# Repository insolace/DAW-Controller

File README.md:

# DAW Controller
 Concept design for a DAW controller with LCD, encoders, and RGB pushbuttons.<br>
 Developed by Eric Bateman

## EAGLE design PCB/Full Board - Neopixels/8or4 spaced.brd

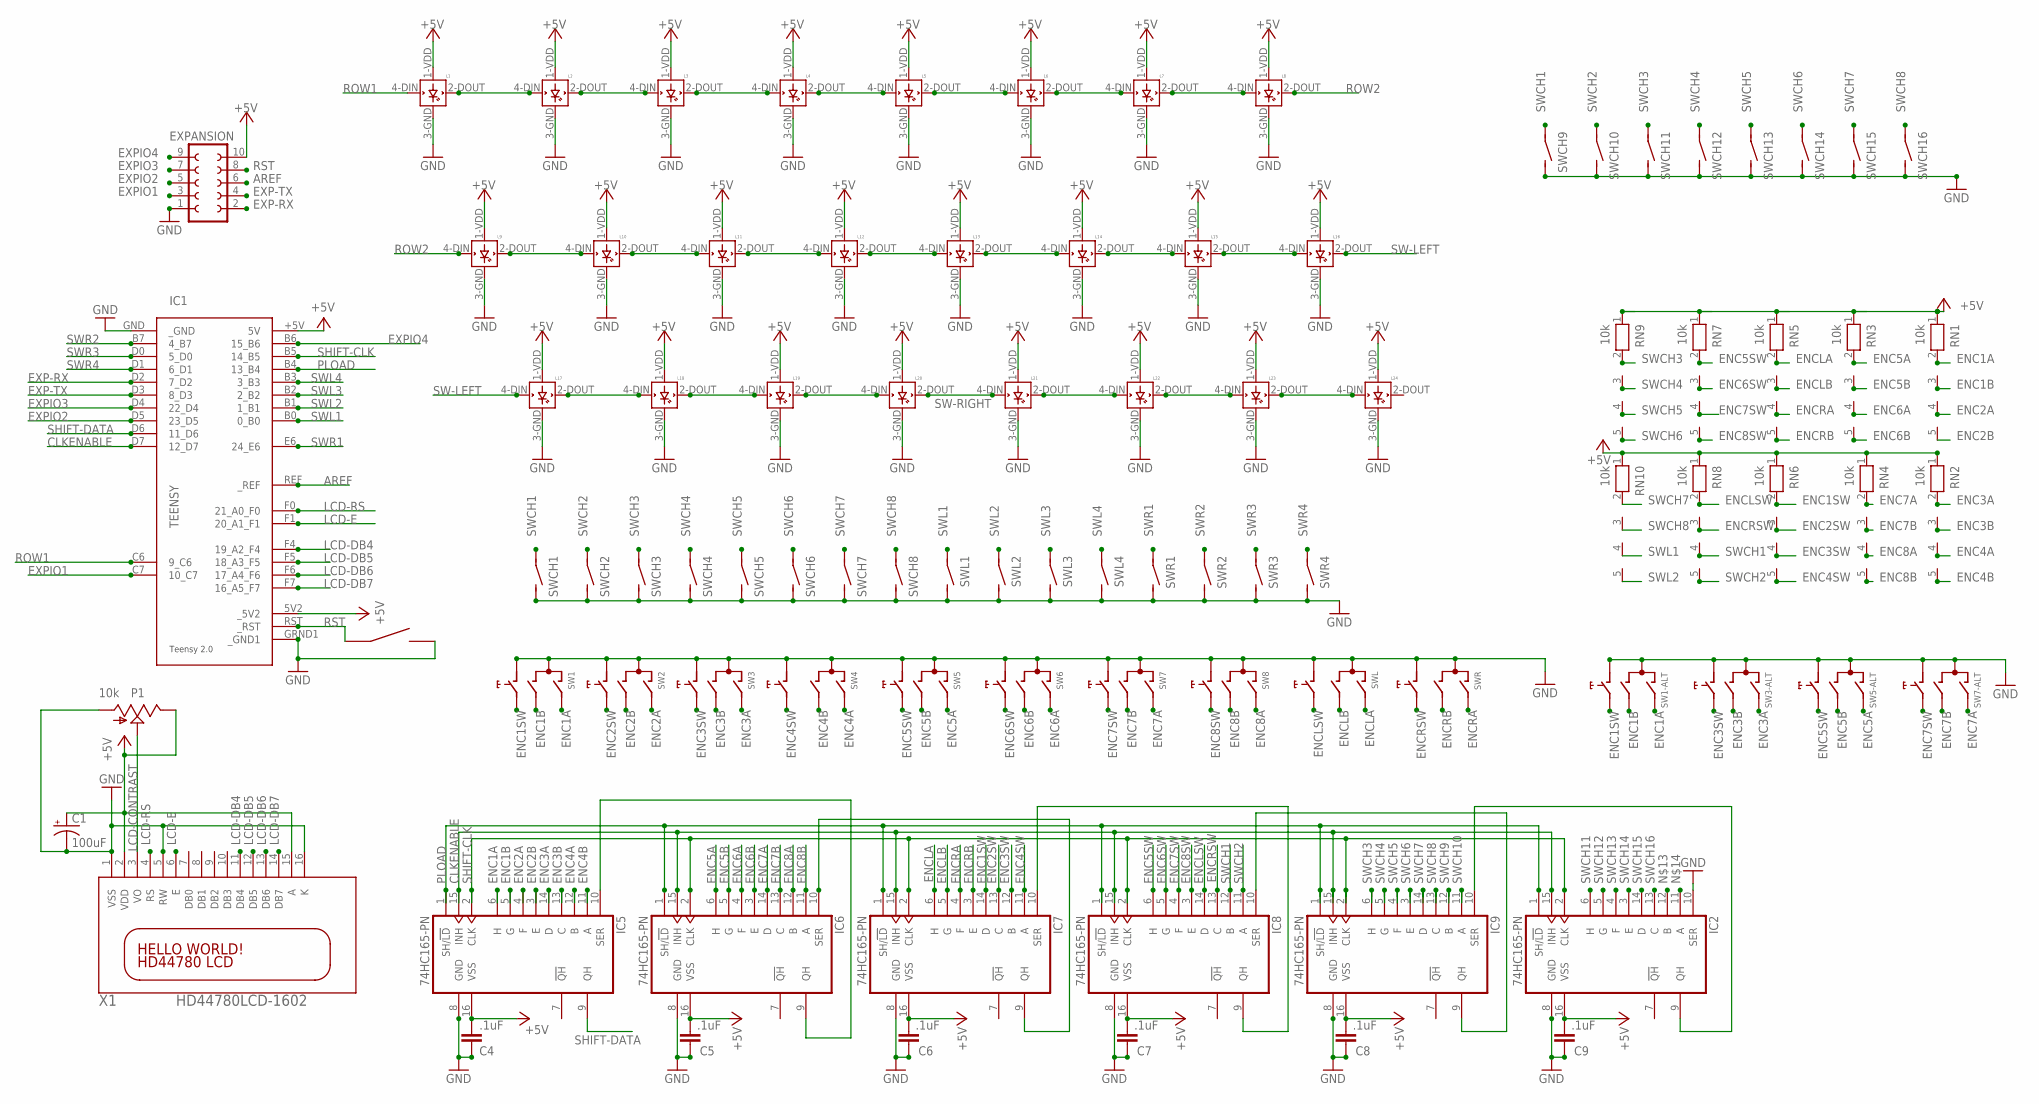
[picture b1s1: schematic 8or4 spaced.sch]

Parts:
C1: 100uF; E2,5-7
C4, C5, C6, C7, C8, C9: .1uF; C5B3.5
EXPANSION: FE05-2
IC1: TEENSY
IC2, IC5, IC6, IC7, IC8, IC9: 74HC165-PN; DIL16
L1, L2, L3, L4, L5, L6, L7, L8, L9, L10, L11, L12, L13, L14, L15, L16, L17, L18, L19, L20, L21, L22, L23, L24: WS2812B
P1: 10k; B25U
RN1, RN2, RN3, RN4, RN5, RN6, RN7, RN8, RN9, RN10: 10k; RN-5
SW1, SW1-ALT, SW2, SW3, SW3-ALT, SW4, SW5, SW5-ALT, SW6, SW7, SW7-ALT, SW8: EC12E_SW; ALPS_EC12E_SW
SWCH1, SWCH2, SWCH3, SWCH4, SWCH5, SWCH6, SWCH7, SWCH8, SWCH9, SWCH10, SWCH11, SWCH12, SWCH13, SWCH14, SWCH15, SWCH16: BPM; BMP
SWL: EC12E_SW; ALPS_EC12E_SW
SWL1, SWL2, SWL3, SWL4: BPM; BMP
SWR: EC12E_SW; ALPS_EC12E_SW
SWR1, SWR2, SWR3, SWR4: BPM; BMP
U$1: RA-TACT; B3F-3100
X1: HD44780LCD-1602; LCD1602

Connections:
+5V: C1.+, C4.1, C5.2, C6.2, C7.2, C8.2, C9.2, EXPANSION.10, IC1.5V2 (_5V2), IC1.+5V (5V), IC2.16 (VSS), IC5.16 (VSS), IC6.16 (VSS), IC7.16 (VSS), IC8.16 (VSS), IC9.16 (VSS), L1.1-VDD (VDD), L2.1-VDD (VDD), L3.1-VDD (VDD), L4.1-VDD (VDD), L5.1-VDD (VDD), L6.1-VDD (VDD), L7.1-VDD (VDD), L8.1-VDD (VDD), L9.1-VDD (VDD), L10.1-VDD (VDD), L11.1-VDD (VDD), L12.1-VDD (VDD), L13.1-VDD (VDD), L14.1-VDD (VDD), L15.1-VDD (VDD), L16.1-VDD (VDD), L17.1-VDD (VDD), L18.1-VDD (VDD), L19.1-VDD (VDD), L20.1-VDD (VDD), L21.1-VDD (VDD), L22.1-VDD (VDD), L23.1-VDD (VDD), L24.1-VDD (VDD), P1.E, RN1.1, RN2.1, RN3.1, RN4.1, RN5.1, RN6.1, RN7.1, RN8.1, RN9.1, RN10.1, X1.2 (VDD), X1.15 (A)
AREF: EXPANSION.6, IC1.REF (_REF)
CLKENABLE: IC1.D7 (12_D7), IC2.15 (INH), IC5.15 (INH), IC6.15 (INH), IC7.15 (INH), IC8.15 (INH), IC9.15 (INH)
ENC1A: IC5.6 (H), RN1.2, SW1.A, SW1-ALT.A
ENC1B: IC5.5 (G), RN1.3, SW1.B, SW1-ALT.B
ENC1SW: IC7.14 (D), RN6.2, SW1.E (2), SW1-ALT.E (2)
ENC2A: IC5.4 (F), RN1.4, SW2.A
ENC2B: IC5.3 (E), RN1.5, SW2.B
ENC2SW: IC7.13 (C), RN6.3, SW2.E (2)
ENC3A: IC5.14 (D), RN2.2, SW3.A, SW3-ALT.A
ENC3B: IC5.13 (C), RN2.3, SW3.B, SW3-ALT.B
ENC3SW: IC7.12 (B), RN6.4, SW3.E (2), SW3-ALT.E (2)
ENC4A: IC5.12 (B), RN2.4, SW4.A
ENC4B: IC5.11 (A), RN2.5, SW4.B
ENC4SW: IC7.11 (A), RN6.5, SW4.E (2)
ENC5A: IC6.6 (H), RN3.2, SW5.A, SW5-ALT.A
ENC5B: IC6.5 (G), RN3.3, SW5.B, SW5-ALT.B
ENC5SW: IC8.6 (H), RN7.2, SW5.E (2), SW5-ALT.E (2)
ENC6A: IC6.4 (F), RN3.4, SW6.A
ENC6B: IC6.3 (E), RN3.5, SW6.B
ENC6SW: IC8.5 (G), RN7.3, SW6.E (2)
ENC7A: IC6.14 (D), RN4.2, SW7.A, SW7-ALT.A
ENC7B: IC6.13 (C), RN4.3, SW7.B, SW7-ALT.B
ENC7SW: IC8.4 (F), RN7.4, SW7.E (2), SW7-ALT.E (2)
ENC8A: IC6.12 (B), RN4.4, SW8.A
ENC8B: IC6.11 (A), RN4.5, SW8.B
ENC8SW: IC8.3 (E), RN7.5, SW8.E (2)
ENCLA: IC7.6 (H), RN5.2, SWL.A
ENCLB: IC7.5 (G), RN5.3, SWL.B
ENCLSW: IC8.14 (D), RN8.2, SWL.E (2)
ENCRA: IC7.4 (F), RN5.4, SWR.A
ENCRB: IC7.3 (E), RN5.5, SWR.B
ENCRSW: IC8.13 (C), RN8.3, SWR.E (2)
EXP-RX: EXPANSION.2, IC1.D2 (7_D2)
EXP-TX: EXPANSION.4, IC1.D3 (8_D3)
EXPIO1: EXPANSION.3, IC1.C7 (10_C7)
EXPIO2: EXPANSION.5, IC1.D5 (23_D5)
EXPIO3: EXPANSION.7, IC1.D4 (22_D4)
EXPIO4: EXPANSION.9, IC1.B6 (15_B6)
GND: C1.-, C4.2, C5.1, C6.1, C7.1, C8.1, C9.1, EXPANSION.1, IC1.GND (_GND), IC1.GRND1 (_GND1), IC2.8 (GND), IC2.10 (SER), IC5.8 (GND), IC6.8 (GND), IC7.8 (GND), IC8.8 (GND), IC9.8 (GND), L1.3-GND (GND), L2.3-GND (GND), L3.3-GND (GND), L4.3-GND (GND), L5.3-GND (GND), L6.3-GND (GND), L7.3-GND (GND), L8.3-GND (GND), L9.3-GND (GND), L10.3-GND (GND), L11.3-GND (GND), L12.3-GND (GND), L13.3-GND (GND), L14.3-GND (GND), L15.3-GND (GND), L16.3-GND (GND), L17.3-GND (GND), L18.3-GND (GND), L19.3-GND (GND), L20.3-GND (GND), L21.3-GND (GND), L22.3-GND (GND), L23.3-GND (GND), L24.3-GND (GND), P1.A, SW1.C, SW1.D (1), SW1-ALT.C, SW1-ALT.D (1), SW2.C, SW2.D (1), SW3.C, SW3.D (1), SW3-ALT.C, SW3-ALT.D (1), SW4.C, SW4.D (1), SW5.C, SW5.D (1), SW5-ALT.C, SW5-ALT.D (1), SW6.C, SW6.D (1), SW7.C, SW7.D (1), SW7-ALT.C, SW7-ALT.D (1), SW8.C, SW8.D (1), SWCH1.1, SWCH2.1, SWCH3.1, SWCH4.1, SWCH5.1, SWCH6.1, SWCH7.1, SWCH8.1, SWCH9.1, SWCH10.1, SWCH11.1, SWCH12.1, SWCH13.1, SWCH14.1, SWCH15.1, SWCH16.1, SWL.C, SWL.D (1), SWL1.1, SWL2.1, SWL3.1, SWL4.1, SWR.C, SWR.D (1), SWR1.1, SWR2.1, SWR3.1, SWR4.1, U$1.P2, X1.1 (VSS), X1.5 (RW), X1.16 (K)
IC6-5: IC5.10 (SER), IC6.9 (QH)
IC7-6: IC6.10 (SER), IC7.9 (QH)
IC8-7: IC7.10 (SER), IC8.9 (QH)
IC9-8: IC8.10 (SER), IC9.9 (QH)
LCD-CONTRAST: P1.S, X1.3 (VO)
LCD-DB4: IC1.F4 (19_A2_F4), X1.11 (DB4)
LCD-DB5: IC1.F5 (18_A3_F5), X1.12 (DB5)
LCD-DB6: IC1.F6 (17_A4_F6), X1.13 (DB6)
LCD-DB7: IC1.F7 (16_A5_F7), X1.14 (DB7)
LCD-E: IC1.F1 (20_A1_F1), X1.6 (E)
LCD-RS: IC1.F0 (21_A0_F0), X1.4 (RS)
unnamed: IC2.9 (QH), IC9.10 (SER)
unnamed: L1.2-DOUT (DOUT), L2.4-DIN (DIN)
unnamed: L2.2-DOUT (DOUT), L3.4-DIN (DIN)
unnamed: L3.2-DOUT (DOUT), L4.4-DIN (DIN)
unnamed: L4.2-DOUT (DOUT), L5.4-DIN (DIN)
unnamed: L5.2-DOUT (DOUT), L6.4-DIN (DIN)
unnamed: L6.2-DOUT (DOUT), L7.4-DIN (DIN)
unnamed: L7.2-DOUT (DOUT), L8.4-DIN (DIN)
unnamed: L9.2-DOUT (DOUT), L10.4-DIN (DIN)
unnamed: L10.2-DOUT (DOUT), L11.4-DIN (DIN)
unnamed: L11.2-DOUT (DOUT), L12.4-DIN (DIN)
unnamed: L12.2-DOUT (DOUT), L13.4-DIN (DIN)
unnamed: L13.2-DOUT (DOUT), L14.4-DIN (DIN)
unnamed: L14.2-DOUT (DOUT), L15.4-DIN (DIN)
unnamed: L15.2-DOUT (DOUT), L16.4-DIN (DIN)
unnamed: L17.2-DOUT (DOUT), L18.4-DIN (DIN)
unnamed: L18.2-DOUT (DOUT), L19.4-DIN (DIN)
unnamed: L19.2-DOUT (DOUT), L20.4-DIN (DIN)
unnamed: L21.2-DOUT (DOUT), L22.4-DIN (DIN)
unnamed: L22.2-DOUT (DOUT), L23.4-DIN (DIN)
unnamed: L23.2-DOUT (DOUT), L24.4-DIN (DIN)
PLOAD: IC1.B4 (13_B4), IC2.1 (SH/!LD), IC5.1 (SH/!LD), IC6.1 (SH/!LD), IC7.1 (SH/!LD), IC8.1 (SH/!LD), IC9.1 (SH/!LD)
ROW1: IC1.C6 (9_C6), L1.4-DIN (DIN)
ROW2: L8.2-DOUT (DOUT), L9.4-DIN (DIN)
RST: EXPANSION.8, IC1.RST (_RST), U$1.P1
SHIFT-CLK: IC1.B5 (14_B5), IC2.2 (CLK), IC5.2 (CLK), IC6.2 (CLK), IC7.2 (CLK), IC8.2 (CLK), IC9.2 (CLK)
SHIFT-DATA: IC1.D6 (11_D6), IC5.9 (QH)
SW-LEFT: L16.2-DOUT (DOUT), L17.4-DIN (DIN)
SW-RIGHT: L20.2-DOUT (DOUT), L21.4-DIN (DIN)
SWCH1: IC8.12 (B), RN8.4, SWCH1.2, SWCH9.2
SWCH2: IC8.11 (A), RN8.5, SWCH2.2, SWCH10.2
SWCH3: IC9.6 (H), RN9.2, SWCH3.2, SWCH11.2
SWCH4: IC9.5 (G), RN9.3, SWCH4.2, SWCH12.2
SWCH5: IC9.4 (F), RN9.4, SWCH5.2, SWCH13.2
SWCH6: IC9.3 (E), RN9.5, SWCH6.2, SWCH14.2
SWCH7: IC9.14 (D), RN10.2, SWCH7.2, SWCH15.2
SWCH8: IC9.13 (C), RN10.3, SWCH8.2, SWCH16.2
SWCH9: IC9.12 (B)
SWCH10: IC9.11 (A)
SWCH11: IC2.6 (H)
SWCH12: IC2.5 (G)
SWCH13: IC2.4 (F)
SWCH14: IC2.3 (E)
SWCH15: IC2.14 (D)
SWCH16: IC2.13 (C)
SWL1: IC1.B0 (0_B0), RN10.4, SWL1.2
SWL2: IC1.B1 (1_B1), RN10.5, SWL2.2
SWL3: IC1.B2 (2_B2), SWL3.2
SWL4: IC1.B3 (3_B3), SWL4.2
SWR1: IC1.E6 (24_E6), SWR1.2
SWR2: IC1.B7 (4_B7), SWR2.2
SWR3: IC1.D0 (5_D0), SWR3.2
SWR4: IC1.D1 (6_D1), SWR4.2

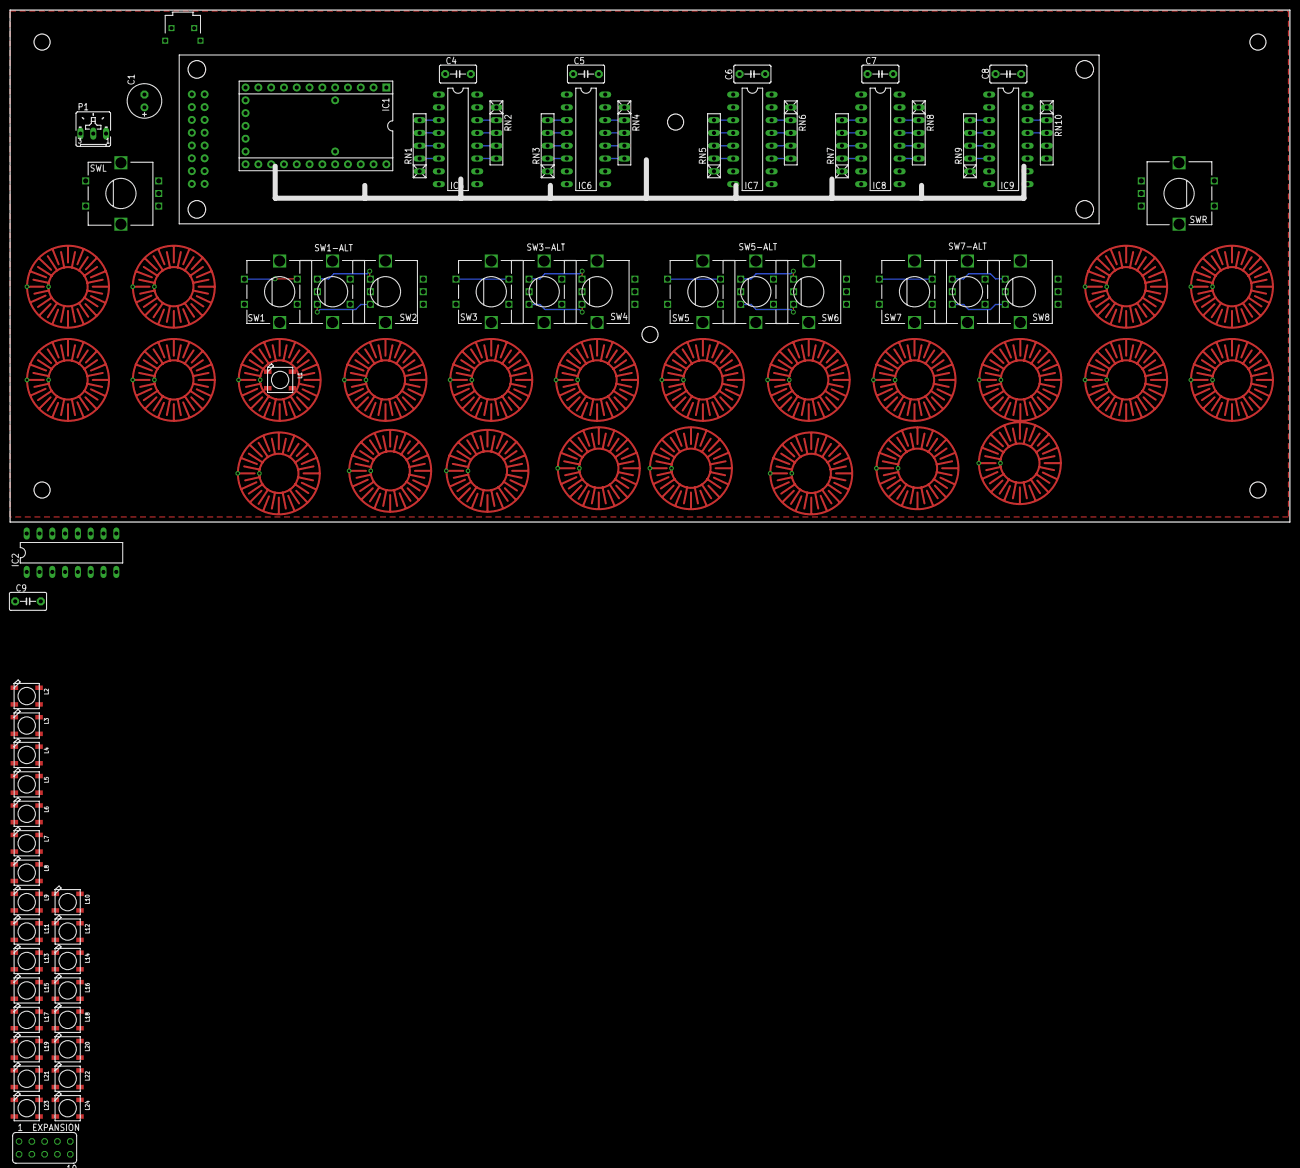
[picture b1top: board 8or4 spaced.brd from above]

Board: 2 copper layers, 254.0 x 101.6 mm, 90 parts (0 on the bottom side), 96 nets.

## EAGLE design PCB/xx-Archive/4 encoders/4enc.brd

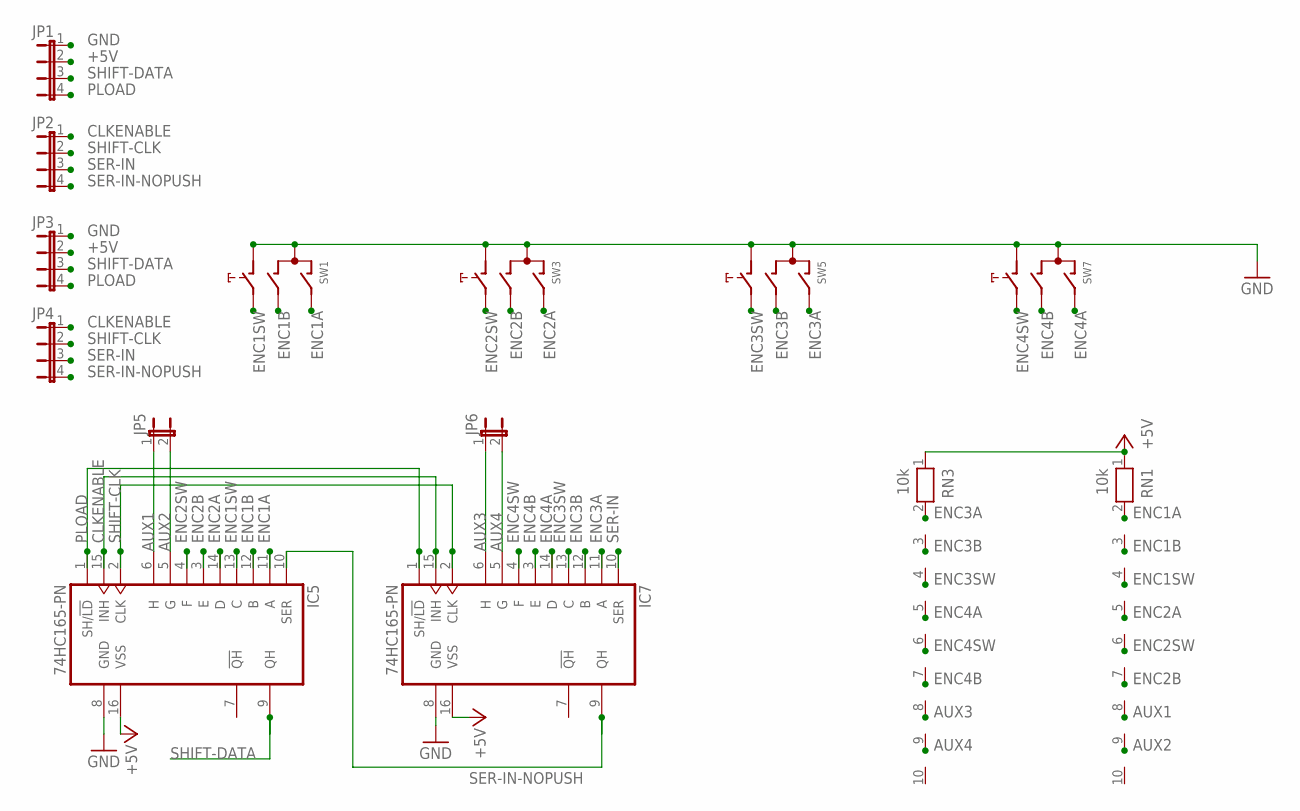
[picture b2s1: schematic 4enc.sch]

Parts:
IC5, IC7: 74HC165-PN; DIL16
JP1, JP2, JP3, JP4: JP4E; JP4
JP5, JP6: JP1E; JP1
RN1, RN3: 10k; RN-10
SW1, SW3, SW5, SW7: EC12E_SW; ALPS_EC12E_SW

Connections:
+5V: IC5.16 (VSS), IC7.16 (VSS), JP1.2, JP3.2, RN1.1, RN3.1
AUX1: IC5.6 (H), JP5.1, RN1.8
AUX2: IC5.5 (G), JP5.2, RN1.9
AUX3: IC7.6 (H), JP6.1, RN3.8
AUX4: IC7.5 (G), JP6.2, RN3.9
CLKENABLE: IC5.15 (INH), IC7.15 (INH), JP2.1, JP4.1
ENC1A: IC5.11 (A), RN1.2, SW1.A
ENC1B: IC5.12 (B), RN1.3, SW1.B
ENC1SW: IC5.13 (C), RN1.4, SW1.E (2)
ENC2A: IC5.14 (D), RN1.5, SW3.A
ENC2B: IC5.3 (E), RN1.7, SW3.B
ENC2SW: IC5.4 (F), RN1.6, SW3.E (2)
ENC3A: IC7.11 (A), RN3.2, SW5.A
ENC3B: IC7.12 (B), RN3.3, SW5.B
ENC3SW: IC7.13 (C), RN3.4, SW5.E (2)
ENC4A: IC7.14 (D), RN3.5, SW7.A
ENC4B: IC7.3 (E), RN3.7, SW7.B
ENC4SW: IC7.4 (F), RN3.6, SW7.E (2)
GND: IC5.8 (GND), IC7.8 (GND), JP1.1, JP3.1, SW1.C, SW1.D (1), SW3.C, SW3.D (1), SW5.C, SW5.D (1), SW7.C, SW7.D (1)
PLOAD: IC5.1 (SH/!LD), IC7.1 (SH/!LD), JP1.4, JP3.4
SER-IN: IC7.10 (SER), JP2.3, JP4.3
SER-IN-NOPUSH: IC5.10 (SER), IC7.9 (QH), JP2.4, JP4.4
SHIFT-CLK: IC5.2 (CLK), IC7.2 (CLK), JP2.2, JP4.2
SHIFT-DATA: IC5.9 (QH), JP1.3, JP3.3

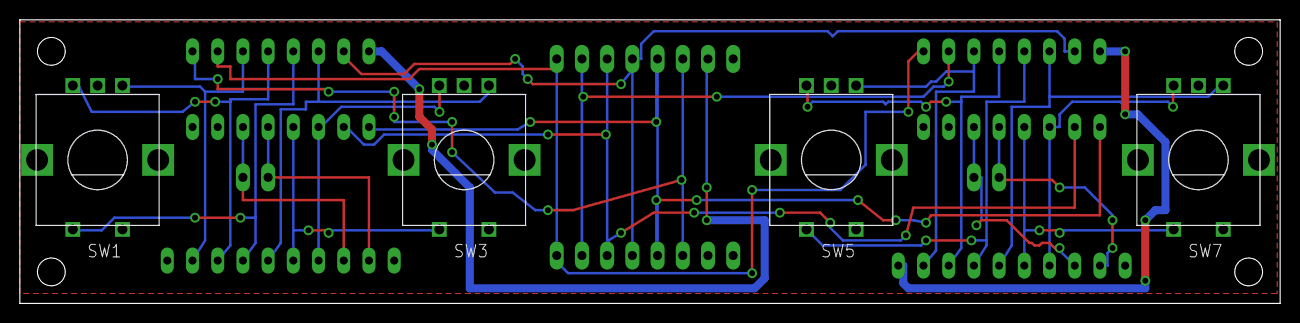
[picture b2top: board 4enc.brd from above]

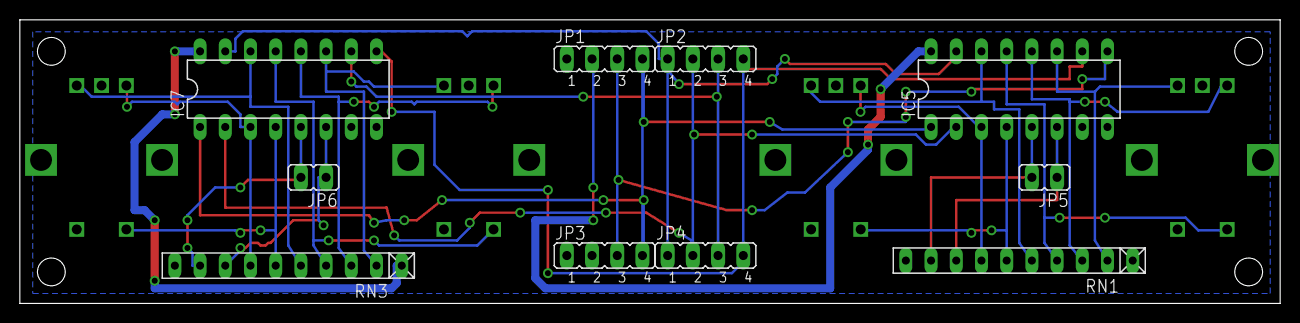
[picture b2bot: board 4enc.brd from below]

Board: 2 copper layers, 127.0 x 28.6 mm, 14 parts (10 on the bottom side), 24 nets.

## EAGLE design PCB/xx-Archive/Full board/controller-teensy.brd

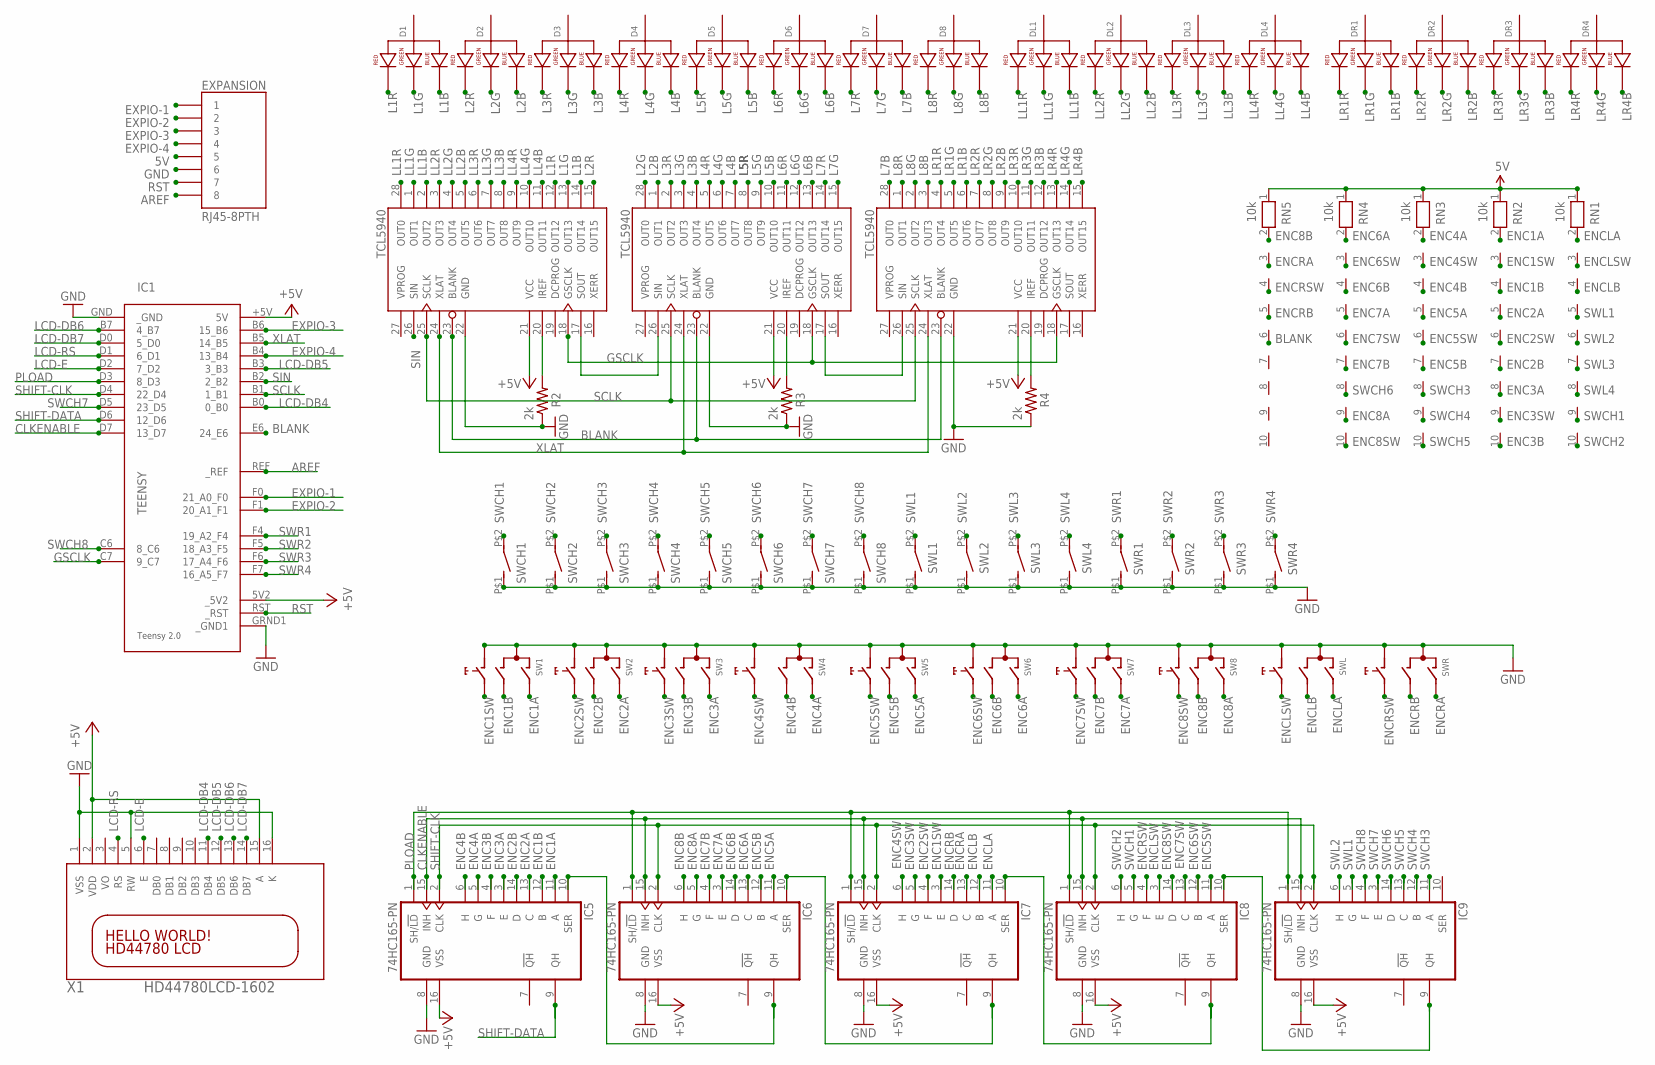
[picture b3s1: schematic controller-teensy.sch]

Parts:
D1, D2, D3, D4, D5, D6, D7, D8: LED-RGB-CA-THRUDIFFUSE; LED-RGB-THRU
DL1, DL2, DL3, DL4: LED-RGB-CA-THRUDIFFUSE; LED-RGB-THRU
DR1, DR2, DR3, DR4: LED-RGB-CA-THRUDIFFUSE; LED-RGB-THRU
EXPANSION: RJ45-8PTH; RJ45-8
IC1: TEENSY
IC2: LEDPWM1; DIP28
IC3: LEDPWM2; DIP28
IC4: LEDPWM3; DIP28
IC5, IC6, IC7, IC8, IC9: 74HC165-PN; DIL16
R2, R3, R4: 2k; 0207/10
RN1, RN2, RN3, RN4, RN5: 10k; RN-10
SW1, SW2, SW3, SW4, SW5, SW6, SW7, SW8: EC12E_SW; ALPS_EC12E_SW
SWCH1, SWCH2, SWCH3, SWCH4, SWCH5, SWCH6, SWCH7, SWCH8: BPM; BMP
SWL: EC12E_SW; ALPS_EC12E_SW
SWL1, SWL2, SWL3, SWL4: BPM; BMP
SWR: EC12E_SW; ALPS_EC12E_SW
SWR1, SWR2, SWR3, SWR4: BPM; BMP
X1: HD44780LCD-1602; LCD1602

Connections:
5V: EXPANSION.5, RN1.1, RN2.1, RN3.1, RN4.1, RN5.1
+5V: IC1.5V2 (_5V2), IC1.+5V (5V), IC2.21 (VCC), IC3.21 (VCC), IC4.21 (VCC), IC5.16 (VSS), IC6.16 (VSS), IC7.16 (VSS), IC8.16 (VSS), IC9.16 (VSS), X1.2 (VDD), X1.15 (A)
AREF: EXPANSION.8, IC1.REF (_REF)
BLANK: IC1.E6 (24_E6), IC2.23 (BLANK), IC3.23 (BLANK), IC4.23 (BLANK), RN5.6
CLKENABLE: IC1.D7 (13_D7), IC5.15 (INH), IC6.15 (INH), IC7.15 (INH), IC8.15 (INH), IC9.15 (INH)
ENC1A: IC5.11 (A), RN2.2, SW1.A
ENC1B: IC5.12 (B), RN2.4, SW1.B
ENC1SW: IC7.3 (E), RN2.3, SW1.E (2)
ENC2A: IC5.13 (C), RN2.5, SW2.A
ENC2B: IC5.14 (D), RN2.7, SW2.B
ENC2SW: IC7.4 (F), RN2.6, SW2.E (2)
ENC3A: IC5.3 (E), RN2.8, SW3.A
ENC3B: IC5.4 (F), RN2.10, SW3.B
ENC3SW: IC7.5 (G), RN2.9, SW3.E (2)
ENC4A: IC5.5 (G), RN3.2, SW4.A
ENC4B: IC5.6 (H), RN3.4, SW4.B
ENC4SW: IC7.6 (H), RN3.3, SW4.E (2)
ENC5A: IC6.11 (A), RN3.5, SW5.A
ENC5B: IC6.12 (B), RN3.7, SW5.B
ENC5SW: IC8.11 (A), RN3.6, SW5.E (2)
ENC6A: IC6.13 (C), RN4.2, SW6.A
ENC6B: IC6.14 (D), RN4.4, SW6.B
ENC6SW: IC8.12 (B), RN4.3, SW6.E (2)
ENC7A: IC6.3 (E), RN4.5, SW7.A
ENC7B: IC6.4 (F), RN4.7, SW7.B
ENC7SW: IC8.13 (C), RN4.6, SW7.E (2)
ENC8A: IC6.5 (G), RN4.9, SW8.A
ENC8B: IC6.6 (H), RN5.2, SW8.B
ENC8SW: IC8.14 (D), RN4.10, SW8.E (2)
ENCLA: IC7.11 (A), RN1.2, SWL.A
ENCLB: IC7.12 (B), RN1.4, SWL.B
ENCLSW: IC8.3 (E), RN1.3, SWL.E (2)
ENCRA: IC7.13 (C), RN5.3, SWR.A
ENCRB: IC7.14 (D), RN5.5, SWR.B
ENCRSW: IC8.4 (F), RN5.4, SWR.E (2)
EXPIO-1: EXPANSION.1, IC1.F0 (21_A0_F0)
EXPIO-2: EXPANSION.2, IC1.F1 (20_A1_F1)
EXPIO-3: EXPANSION.3, IC1.B6 (15_B6)
EXPIO-4: EXPANSION.4, IC1.B4 (13_B4)
GND: EXPANSION.6, IC1.GND (_GND), IC1.GRND1 (_GND1), IC2.22 (GND), IC3.22 (GND), IC4.22 (GND), IC5.8 (GND), IC6.8 (GND), IC7.8 (GND), IC8.8 (GND), IC9.8 (GND), R2.1, R3.1, R4.1, SW1.C, SW1.D (1), SW2.C, SW2.D (1), SW3.C, SW3.D (1), SW4.C, SW4.D (1), SW5.C, SW5.D (1), SW6.C, SW6.D (1), SW7.C, SW7.D (1), SW8.C, SW8.D (1), SWCH1.P$1 (1), SWCH2.P$1 (1), SWCH3.P$1 (1), SWCH4.P$1 (1), SWCH5.P$1 (1), SWCH6.P$1 (1), SWCH7.P$1 (1), SWCH8.P$1 (1), SWL.C, SWL.D (1), SWL1.P$1 (1), SWL2.P$1 (1), SWL3.P$1 (1), SWL4.P$1 (1), SWR.C, SWR.D (1), SWR1.P$1 (1), SWR2.P$1 (1), SWR3.P$1 (1), SWR4.P$1 (1), X1.1 (VSS), X1.5 (RW), X1.16 (K)
GSCLK: IC1.C7 (9_C7), IC2.18 (GSCLK), IC3.18 (GSCLK), IC4.18 (GSCLK)
L1B: D1.4 (BLUE_CATHODE), IC2.14 (OUT14)
L1G: D1.3 (GREEN_CATHODE), IC2.13 (OUT13)
L1R: D1.1 (RED_CATHODE), IC2.12 (OUT12)
L2B: D2.4 (BLUE_CATHODE), IC3.1 (OUT1)
L2G: D2.3 (GREEN_CATHODE), IC3.28 (OUT0)
L2R: D2.1 (RED_CATHODE), IC2.15 (OUT15)
L3B: D3.4 (BLUE_CATHODE), IC3.4 (OUT4)
L3G: D3.3 (GREEN_CATHODE), IC3.3 (OUT3)
L3R: D3.1 (RED_CATHODE), IC3.2 (OUT2)
L4B: D4.4 (BLUE_CATHODE), IC3.7 (OUT7)
L4G: D4.3 (GREEN_CATHODE), IC3.6 (OUT6)
L4R: D4.1 (RED_CATHODE), IC3.5 (OUT5)
L5B: D5.4 (BLUE_CATHODE), IC3.10 (OUT10)
L5G: D5.3 (GREEN_CATHODE), IC3.9 (OUT9)
L5R: D5.1 (RED_CATHODE), IC3.8 (OUT8)
L6B: D6.4 (BLUE_CATHODE), IC3.13 (OUT13)
L6G: D6.3 (GREEN_CATHODE), IC3.12 (OUT12)
L6R: D6.1 (RED_CATHODE), IC3.11 (OUT11)
L7B: D7.4 (BLUE_CATHODE), IC4.28 (OUT0)
L7G: D7.3 (GREEN_CATHODE), IC3.15 (OUT15)
L7R: D7.1 (RED_CATHODE), IC3.14 (OUT14)
L8B: D8.4 (BLUE_CATHODE), IC4.3 (OUT3)
L8G: D8.3 (GREEN_CATHODE), IC4.2 (OUT2)
L8R: D8.1 (RED_CATHODE), IC4.1 (OUT1)
LCD-DB4: IC1.B0 (0_B0), X1.11 (DB4)
LCD-DB5: IC1.B3 (3_B3), X1.12 (DB5)
LCD-DB6: IC1.B7 (4_B7), X1.13 (DB6)
LCD-DB7: IC1.D0 (5_D0), X1.14 (DB7)
LCD-E: IC1.D2 (7_D2), X1.6 (E)
LCD-RS: IC1.D1 (6_D1), X1.4 (RS)
LL1B: DL1.4 (BLUE_CATHODE), IC2.2 (OUT2)
LL1G: DL1.3 (GREEN_CATHODE), IC2.1 (OUT1)
LL1R: DL1.1 (RED_CATHODE), IC2.28 (OUT0)
LL2B: DL2.4 (BLUE_CATHODE), IC2.5 (OUT5)
LL2G: DL2.3 (GREEN_CATHODE), IC2.4 (OUT4)
LL2R: DL2.1 (RED_CATHODE), IC2.3 (OUT3)
LL3B: DL3.4 (BLUE_CATHODE), IC2.8 (OUT8)
LL3G: DL3.3 (GREEN_CATHODE), IC2.7 (OUT7)
LL3R: DL3.1 (RED_CATHODE), IC2.6 (OUT6)
LL4B: DL4.4 (BLUE_CATHODE), IC2.11 (OUT11)
LL4G: DL4.3 (GREEN_CATHODE), IC2.10 (OUT10)
LL4R: DL4.1 (RED_CATHODE), IC2.9 (OUT9)
LR1B: DR1.4 (BLUE_CATHODE), IC4.6 (OUT6)
LR1G: DR1.3 (GREEN_CATHODE), IC4.5 (OUT5)
LR1R: DR1.1 (RED_CATHODE), IC4.4 (OUT4)
LR2B: DR2.4 (BLUE_CATHODE), IC4.9 (OUT9)
LR2G: DR2.3 (GREEN_CATHODE), IC4.8 (OUT8)
LR2R: DR2.1 (RED_CATHODE), IC4.7 (OUT7)
LR3B: DR3.4 (BLUE_CATHODE), IC4.12 (OUT12)
LR3G: DR3.3 (GREEN_CATHODE), IC4.11 (OUT11)
LR3R: DR3.1 (RED_CATHODE), IC4.10 (OUT10)
LR4B: DR4.4 (BLUE_CATHODE), IC4.15 (OUT15)
LR4G: DR4.3 (GREEN_CATHODE), IC4.14 (OUT14)
LR4R: DR4.1 (RED_CATHODE), IC4.13 (OUT13)
unnamed: IC3.20 (IREF), R3.2
unnamed: IC2.20 (IREF), R2.2
unnamed: IC2.17 (SOUT), IC3.26 (SIN)
unnamed: IC3.17 (SOUT), IC4.26 (SIN)
unnamed: IC4.20 (IREF), R4.2
unnamed: IC5.10 (SER), IC6.9 (QH)
unnamed: IC6.10 (SER), IC7.9 (QH)
unnamed: IC7.10 (SER), IC8.9 (QH)
unnamed: IC8.10 (SER), IC9.9 (QH)
PLOAD: IC1.D3 (8_D3), IC5.1 (SH/!LD), IC6.1 (SH/!LD), IC7.1 (SH/!LD), IC8.1 (SH/!LD), IC9.1 (SH/!LD)
RST: EXPANSION.7, IC1.RST (_RST)
SCLK: IC1.B1 (1_B1), IC2.25 (SCLK), IC3.25 (SCLK), IC4.25 (SCLK)
SHIFT-CLK: IC1.D4 (22_D4), IC5.2 (CLK), IC6.2 (CLK), IC7.2 (CLK), IC8.2 (CLK), IC9.2 (CLK)
SHIFT-DATA: IC1.D6 (12_D6), IC5.9 (QH)
SIN: IC1.B2 (2_B2), IC2.26 (SIN)
SWCH1: IC8.5 (G), RN1.9, SWCH1.P$2 (2)
SWCH2: IC8.6 (H), RN1.10, SWCH2.P$2 (2)
SWCH3: IC9.11 (A), RN3.8, SWCH3.P$2 (2)
SWCH4: IC9.12 (B), RN3.9, SWCH4.P$2 (2)
SWCH5: IC9.13 (C), RN3.10, SWCH5.P$2 (2)
SWCH6: IC9.14 (D), RN4.8, SWCH6.P$2 (2)
SWCH7: IC1.D5 (23_D5), IC9.3 (E), SWCH7.P$2 (2)
SWCH8: IC1.C6 (8_C6), IC9.4 (F), SWCH8.P$2 (2)
SWL1: IC9.5 (G), RN1.5, SWL1.P$2 (2)
SWL2: IC9.6 (H), RN1.6, SWL2.P$2 (2)
SWL3: RN1.7, SWL3.P$2 (2)
SWL4: RN1.8, SWL4.P$2 (2)
SWR1: IC1.F4 (19_A2_F4), SWR1.P$2 (2)
SWR2: IC1.F5 (18_A3_F5), SWR2.P$2 (2)
SWR3: IC1.F6 (17_A4_F6), SWR3.P$2 (2)
SWR4: IC1.F7 (16_A5_F7), SWR4.P$2 (2)
XLAT: IC1.B5 (14_B5), IC2.24 (XLAT), IC3.24 (XLAT), IC4.24 (XLAT)

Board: 2 copper layers, 61 parts (2 on the bottom side), 127 nets, no tracks yet.

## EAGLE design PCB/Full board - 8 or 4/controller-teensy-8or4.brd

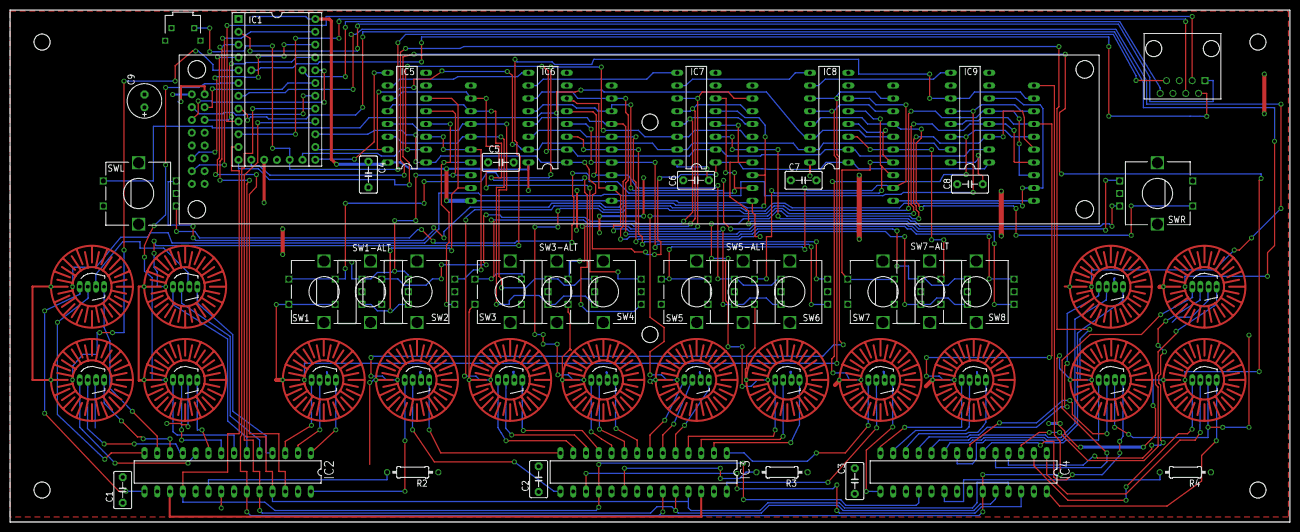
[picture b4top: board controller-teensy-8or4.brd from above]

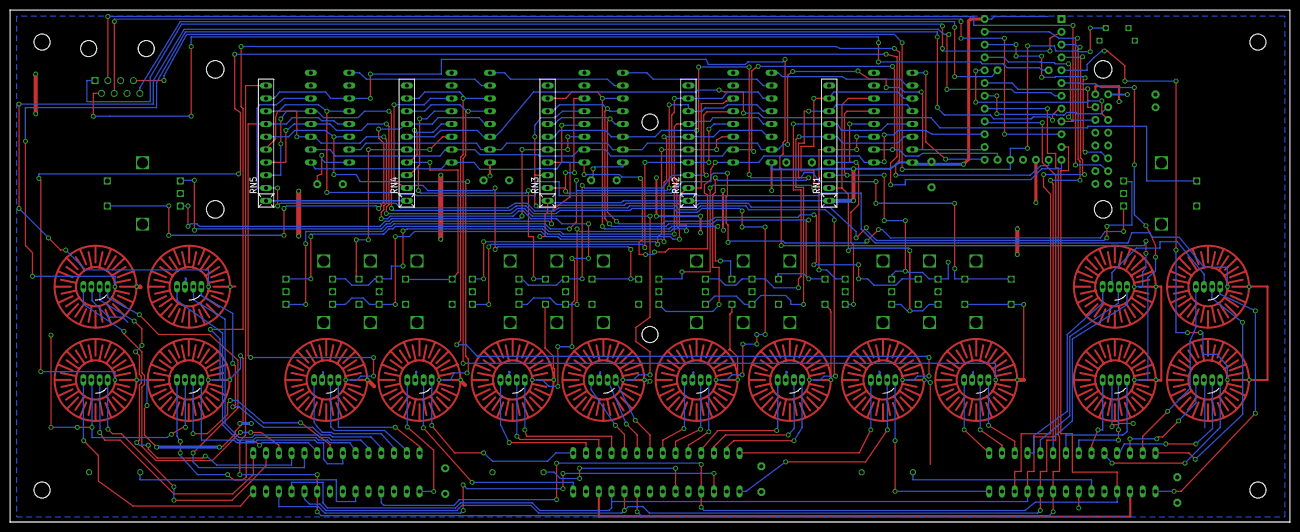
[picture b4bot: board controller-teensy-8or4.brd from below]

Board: 2 copper layers, 254.0 x 101.6 mm, 75 parts (5 on the bottom side), 126 nets.

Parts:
C1, C2, C3, C4, C5, C6, C7, C8: .1uF; C5B3.5
C9: 100uF; E2,5-7
D1, D2, D3, D4, D5, D6, D7, D8: LED-RGB-CA-THRUDIFFUSE; LED-RGB-THRU
DL1, DL2, DL3, DL4: LED-RGB-CA-THRUDIFFUSE; LED-RGB-THRU
DR1, DR2, DR3, DR4: LED-RGB-CA-THRUDIFFUSE; LED-RGB-THRU
EXPANSION: RJ45-8PTH; RJ45-8
IC1: TEENSY
IC2: LEDPWM1; DIP28
IC3: LEDPWM2; DIP28
IC4: LEDPWM3; DIP28
IC5, IC6, IC7, IC8, IC9: 74HC165-PN; DIL16
R2, R3, R4: 2k; 0207/10
RN1, RN2, RN3, RN4, RN5: 10k; RN-10
SW1, SW1-ALT, SW2, SW3, SW3-ALT, SW4, SW5, SW5-ALT, SW6, SW7, SW7-ALT, SW8: EC12E_SW; ALPS_EC12E_SW
SWCH1, SWCH2, SWCH3, SWCH4, SWCH5, SWCH6, SWCH7, SWCH8: BMP
SWL: EC12E_SW; ALPS_EC12E_SW
SWL1, SWL2, SWL3, SWL4: BMP
SWR: EC12E_SW; ALPS_EC12E_SW
SWR1, SWR2, SWR3, SWR4: BMP
U$1: RA-TACT; B3F-3100
X1: HD44780LCD-1602; LCD1602

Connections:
+5V: C1.2, C2.2, C3.2, C4.1, C5.2, C6.2, C7.2, C8.2, C9.+, D1.2, D2.2, D3.2, D4.2, D5.2, D6.2, D7.2, D8.2, DL1.2, DL2.2, DL3.2, DL4.2, DR1.2, DR2.2, DR3.2, DR4.2, EXPANSION.5, IC1.5V2, IC1.+5V, IC2.19, IC2.21, IC3.19, IC3.21, IC4.19, IC4.21, IC5.16, IC6.16, IC7.16, IC8.16, IC9.16, RN1.1, RN2.1, RN3.1, RN4.1, RN5.1, X1.2, X1.15
AREF: EXPANSION.8, IC1.REF
BLANK: IC1.B6, IC2.23, IC3.23, IC4.23, RN5.10
CLKENABLE: IC1.D7, IC5.15, IC6.15, IC7.15, IC8.15, IC9.15
ENC1A: IC5.6, RN1.2, SW1.A, SW1-ALT.A
ENC1B: IC5.5, RN1.3, SW1.B, SW1-ALT.B
ENC1SW: IC7.14, RN3.6, SW1.E, SW1-ALT.E
ENC2A: IC5.4, RN1.4, SW2.A
ENC2B: IC5.3, RN1.5, SW2.B
ENC2SW: IC7.13, RN3.7, SW2.E
ENC3A: IC5.14, RN1.6, SW3.A, SW3-ALT.A
ENC3B: IC5.13, RN1.7, SW3.B, SW3-ALT.B
ENC3SW: IC7.12, RN3.8, SW3.E, SW3-ALT.E
ENC4A: IC5.12, RN1.8, SW4.A
ENC4B: IC5.11, RN1.9, SW4.B
ENC4SW: IC7.11, RN3.9, SW4.E
ENC5A: IC6.6, RN2.2, SW5.A, SW5-ALT.A
ENC5B: IC6.5, RN2.3, SW5.B, SW5-ALT.B
ENC5SW: IC8.6, RN4.2, SW5.E, SW5-ALT.E
ENC6A: IC6.4, RN2.4, SW6.A
ENC6B: IC6.3, RN2.5, SW6.B
ENC6SW: IC8.5, RN4.3, SW6.E
ENC7A: IC6.14, RN2.6, SW7.A, SW7-ALT.A
ENC7B: IC6.13, RN2.7, SW7.B, SW7-ALT.B
ENC7SW: IC8.4, RN4.4, SW7.E, SW7-ALT.E
ENC8A: IC6.12, RN2.8, SW8.A
ENC8B: IC6.11, RN2.9, SW8.B
ENC8SW: IC8.3, RN4.5, SW8.E
ENCLA: IC7.6, RN3.2, SWL.A
ENCLB: IC7.5, RN3.3, SWL.B
ENCLSW: IC8.14, RN4.6, SWL.E
ENCRA: IC7.4, RN3.4, SWR.A
ENCRB: IC7.3, RN3.5, SWR.B
ENCRSW: IC8.13, RN4.7, SWR.E
EXPIO-1: EXPANSION.1, IC1.B0
EXPIO-2: EXPANSION.2, IC1.E6
EXPIO-3-RX: EXPANSION.3, IC1.D2
EXPIO-4-TX: EXPANSION.4, IC1.D3
GND: C1.1, C2.1, C3.1, C4.2, C5.1, C6.1, C7.1, C8.1, C9.-, EXPANSION.6, IC1.GND, IC1.GRND1, IC2.22, IC2.27, IC3.22, IC3.27, IC4.22, IC4.27, IC5.8, IC6.8, IC7.8, IC8.8, IC9.8, IC9.10, R2.1, R3.1, R4.1, SW1.C, SW1.D, SW1-ALT.C, SW1-ALT.D, SW2.C, SW2.D, SW3.C, SW3.D, SW3-ALT.C, SW3-ALT.D, SW4.C, SW4.D, SW5.C, SW5.D, SW5-ALT.C, SW5-ALT.D, SW6.C, SW6.D, SW7.C, SW7.D, SW7-ALT.C, SW7-ALT.D, SW8.C, SW8.D, SWCH1.1, SWCH2.1, SWCH3.1, SWCH4.1, SWCH5.1, SWCH6.1, SWCH7.1, SWCH8.1, SWL.C, SWL.D, SWL1.1, SWL2.1, SWL3.1, SWL4.1, SWR.C, SWR.D, SWR1.1, SWR2.1, SWR3.1, SWR4.1, U$1.P2, X1.1, X1.5, X1.16
GSCLK: IC1.C6, IC2.18, IC3.18, IC4.18
IC6-5: IC5.10, IC6.9
IC7-6: IC6.10, IC7.9
IC8-7: IC7.10, IC8.9
IC9-8: IC8.10, IC9.9
L1B: D1.4, IC2.3
L1G: D1.3, IC2.2
L1R: D1.1, IC2.1
L2B: D2.4, IC2.28
L2G: D2.3, IC3.15
L2R: D2.1, IC3.14
L3B: D3.4, IC3.13
L3G: D3.3, IC3.12
L3R: D3.1, IC3.11
L4B: D4.4, IC3.10
L4G: D4.3, IC3.9
L4R: D4.1, IC3.8
L5B: D5.4, IC3.7
L5G: D5.3, IC3.6
L5R: D5.1, IC3.5
L6B: D6.4, IC3.4
L6G: D6.3, IC3.3
L6R: D6.1, IC3.2
L7B: D7.4, IC3.1
L7G: D7.3, IC3.28
L7R: D7.1, IC4.15
L8B: D8.4, IC4.14
L8G: D8.3, IC4.13
L8R: D8.1, IC4.12
LCD-DB4: IC1.F4, X1.11
LCD-DB5: IC1.F5, X1.12
LCD-DB6: IC1.F6, X1.13
LCD-DB7: IC1.F7, X1.14
LCD-E: IC1.F1, X1.6
LCD-RS: IC1.F0, X1.4
LL1B: DL1.4, IC2.15
LL1G: DL1.3, IC2.14
LL1R: DL1.1, IC2.13
LL2B: DL2.4, IC2.6
LL2G: DL2.3, IC2.5
LL2R: DL2.1, IC2.4
LL3B: DL3.4, IC2.10
LL3G: DL3.3, IC2.11
LL3R: DL3.1, IC2.12
LL4B: DL4.4, IC2.7
LL4G: DL4.3, IC2.8
LL4R: DL4.1, IC2.9
LR1B: DR1.4, IC4.11
LR1G: DR1.3, IC4.10
LR1R: DR1.1, IC4.9
LR2B: DR2.4, IC4.5
LR2G: DR2.3, IC4.4
LR2R: DR2.1, IC4.3
LR3B: DR3.4, IC4.8
LR3G: DR3.3, IC4.7
LR3R: DR3.1, IC4.6
LR4B: DR4.4, IC4.2
LR4G: DR4.3, IC4.1
LR4R: DR4.1, IC4.28
unnamed: IC3.20, R3.2
unnamed: IC2.20, R2.2
unnamed: IC2.17, IC3.26
unnamed: IC3.17, IC4.26
unnamed: IC4.20, R4.2
PLOAD: IC1.B4, IC5.1, IC6.1, IC7.1, IC8.1, IC9.1
RST: EXPANSION.7, IC1.RST, U$1.P1
SCLK: IC1.B1, IC2.25, IC3.25, IC4.25
SHIFT-CLK: IC1.D4, IC5.2, IC6.2, IC7.2, IC8.2, IC9.2
SHIFT-DATA: IC1.D6, IC5.9
SIN: IC1.B2, IC2.26
SWCH1: IC8.12, RN4.8, SWCH1.2
SWCH2: IC8.11, RN4.9, SWCH2.2
SWCH3: IC9.6, RN5.2, SWCH3.2
SWCH4: IC9.5, RN5.3, SWCH4.2
SWCH5: IC9.4, RN5.4, SWCH5.2
SWCH6: IC9.3, RN5.5, SWCH6.2
SWCH7: IC9.14, RN5.6, SWCH7.2
SWCH8: IC9.13, RN5.7, SWCH8.2
SWL1: IC9.12, RN5.8, SWL1.2
SWL2: IC9.11, RN5.9, SWL2.2
SWL3: IC1.B3, SWL3.2
SWL4: IC1.B7, SWL4.2
SWR1: IC1.D0, SWR1.2
SWR2: IC1.D1, SWR2.2
SWR3: IC1.D5, SWR3.2
SWR4: IC1.C7, SWR4.2
XLAT: IC1.B5, IC2.24, IC3.24, IC4.24

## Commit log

2020-03-12 Add graphics
2020-03-12 Remove symlink

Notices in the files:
parts and their libraries:
teensy: Licensed Under Creative Commons Attribution-ShareAlike 3.0 Unported (CC BY-SA 3.0)
SparkFun-LED: Licensing: CC v3.0 Share-Alike You are welcome to use this library for commercial purposes.
